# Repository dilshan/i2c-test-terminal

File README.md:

# I2C Master Mode Emulator

The I2C master mode emulator allows communication with I2C devices by sending or receiving data to/from the I2C bus. To issue the I2C commands, the emulator should connect to a PC over the USB port. After initializing the emulator, the PC and directly control the I2C slave chip/module.

This emulator is based on [ATmega16A](https://www.microchip.com/wwwproducts/en/ATmega16A) MCU. The USB communication channel is develop using the [V-USB](https://www.obdev.at/products/vusb/index.html) firmware.

To simplify the assembly, the PCB of this emulator is designed on a single-side board. The dimensions of the PCB are 96.77mm × 110.73mm. All the parts used in this project are through-hole-type, generally available components.

This emulator needs an external power supply, and the recommended supply voltage is between 12V - 15V.

The control software of the emulator is developed using libusb and tested only with *Linux* operating systems. The current firmware and control software support I2C emulation on 100kHz, 250kHz, and 400kHz clock rates.

Initially, we develop this emulator to work with 5V I2C devices, but later it has extended to work with 3.3V I2C devices. The 3.3V design is still under testing, and at the prototyping stage, we found a couple of issues in 3.3V mode.

In 3.3V mode, the required output level is available only if the emulator is in a "*ready*" state. In all the other states, it provides 5V output. **Therefore in 3.3V mode, necessary precautions need to be taken to protect the slave device from over-voltage damages.**

This project is an open-source hardware project. All the content of this project are distributed under the terms of the following license:

-   Hardware License: [CC BY 4.0](https://creativecommons.org/licenses/by/4.0/)
-   Software and firmware License: [MIT](https://github.com/dilshan/i2c-test-terminal/blob/main/LICENSE)
-   [Documentation](https://github.com/dilshan/i2c-test-terminal/wiki) License: [CC BY 4.0](https://creativecommons.org/licenses/by/4.0/)

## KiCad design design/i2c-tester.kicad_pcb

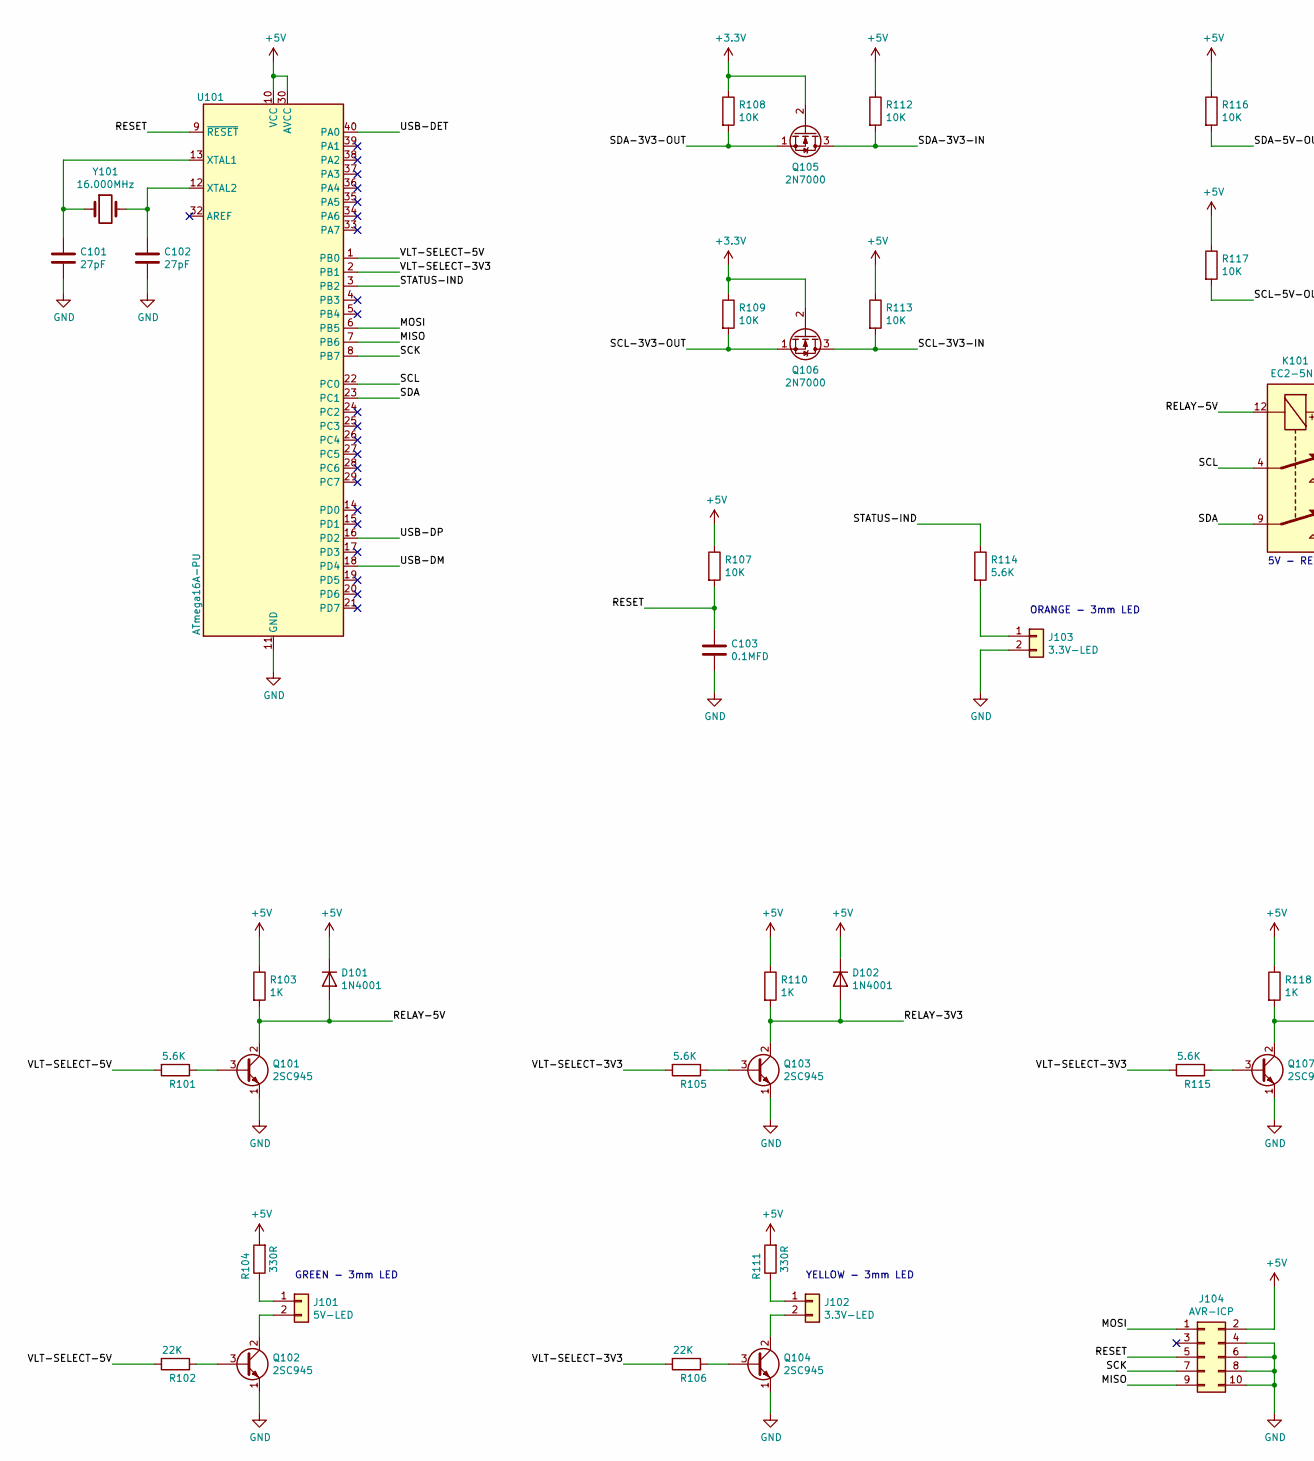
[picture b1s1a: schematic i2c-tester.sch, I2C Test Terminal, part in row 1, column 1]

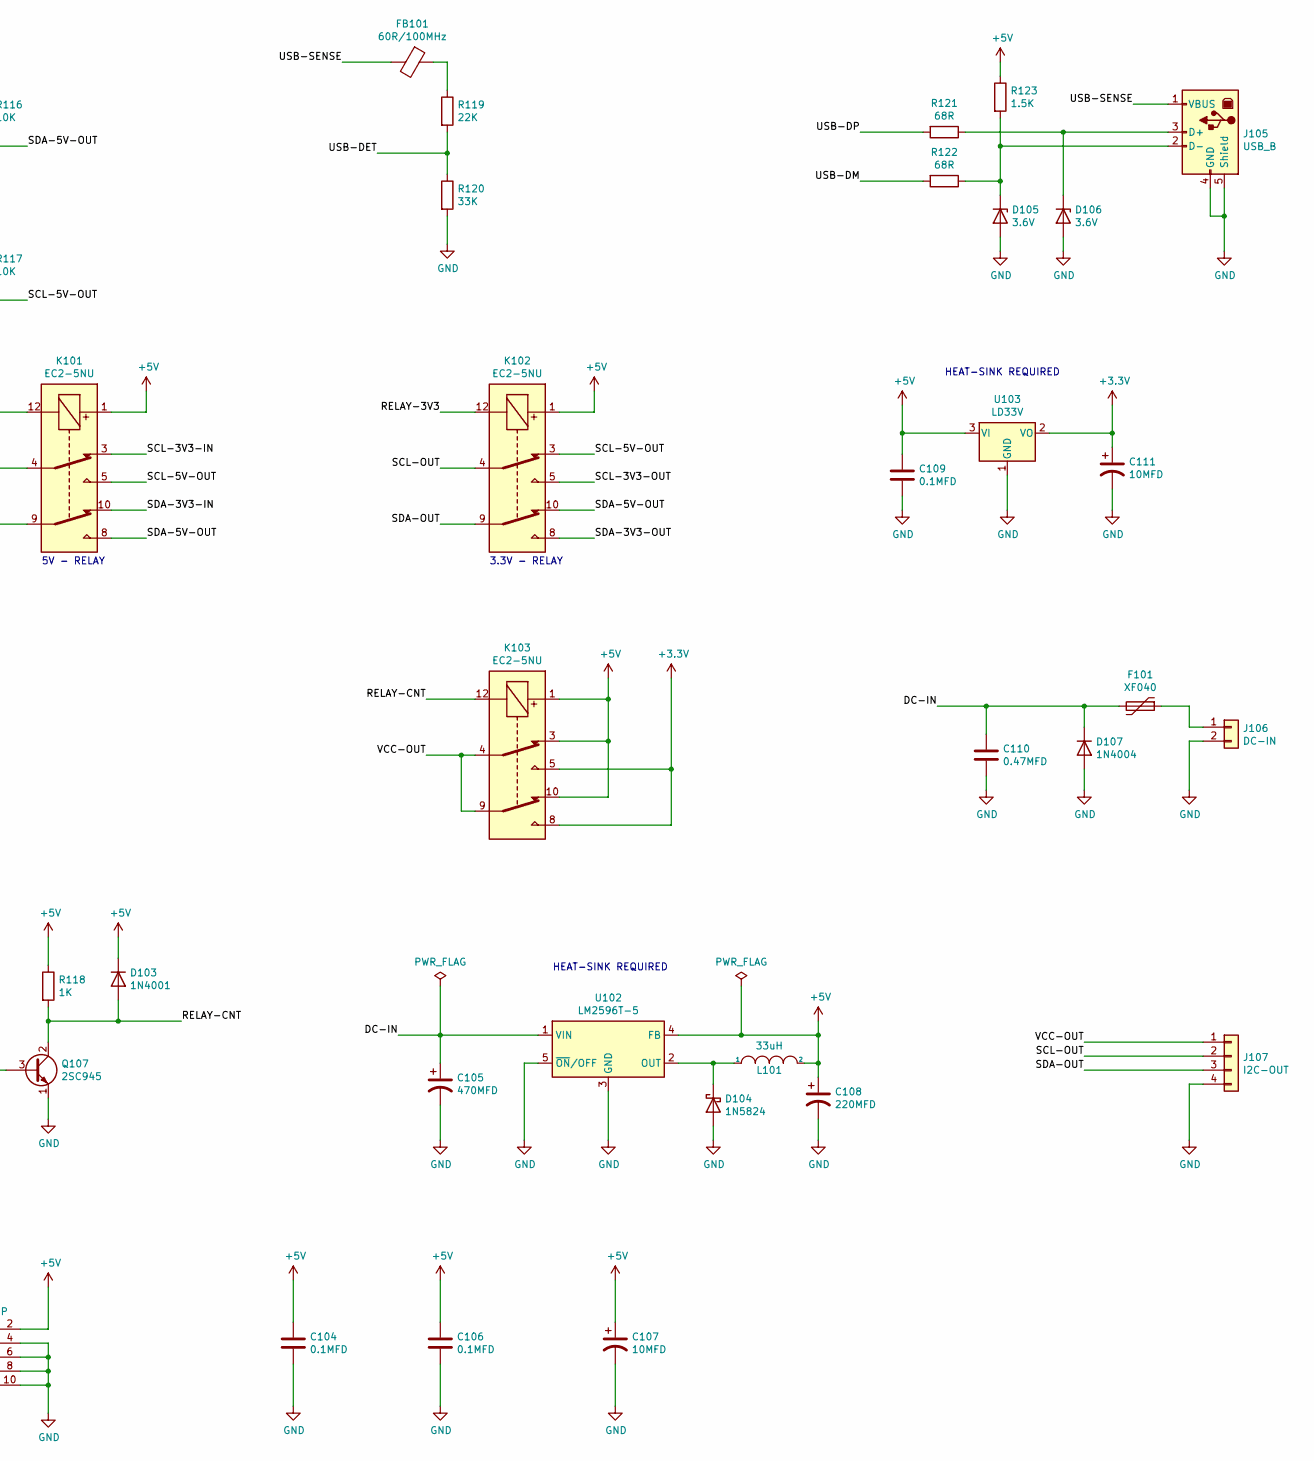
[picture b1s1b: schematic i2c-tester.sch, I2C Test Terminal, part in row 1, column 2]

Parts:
C101, C102: 27pF; C_Disc_D5.0mm_W2.5mm_P2.50mm
C103, C104, C106, C109: 0.1MFD; C_Disc_D12.5mm_W5.0mm_P10.00mm
C105: 470MFD; CP_Radial_D8.0mm_P3.50mm
C107, C111: 10MFD; CP_Radial_D5.0mm_P2.00mm
C108: 220MFD; CP_Radial_D6.3mm_P2.50mm
C110: 0.47MFD; C_Rect_L16.5mm_W7.0mm_P15.00mm_MKT
D101, D102, D103: 1N4001; D_DO-41_SOD81_P10.16mm_Horizontal
D104: 1N5824; D_DO-41_SOD81_P10.16mm_Horizontal
D105, D106: 3.6V; D_DO-35_SOD27_P7.62mm_Horizontal
D107: 1N4004; D_DO-41_SOD81_P10.16mm_Horizontal
F101: XF040; Fuse_Bourns_MF-RG300
FB101: 60R/100MHz; L_Axial_L6.6mm_D2.7mm_P10.16mm_Horizontal_Vishay_IM-2
J101: 5V-LED; PinHeader_1x02_P2.54mm_Vertical
J102, J103: 3.3V-LED; PinHeader_1x02_P2.54mm_Vertical
J104: AVR-ICP; PinHeader_2x05_P2.54mm_Vertical
J105: USB_B; USB_B_Lumberg_2411_02_Horizontal
J106: DC-IN; PhoenixContact_MCV_1,5_2-G-5.08_1x02_P5.08mm_Vertical
J107: I2C-OUT; PinHeader_1x04_P2.54mm_Vertical
K101, K102, K103: EC2-5NU; Relay_DPDT_Kemet_EC2
L101: 33uH; L_Toroid_Vertical_L14.0mm_W5.6mm_P5.30mm_Bourns_5700
Q101, Q102, Q103, Q104, Q107: 2SC945; TO-92_HandSolder
Q105, Q106: 2N7000; TO-92_HandSolder
R101, R105, R114, R115: 5.6K; R_Axial_DIN0309_L9.0mm_D3.2mm_P15.24mm_Horizontal
R102, R106, R119: 22K; R_Axial_DIN0309_L9.0mm_D3.2mm_P15.24mm_Horizontal
R103, R110, R118: 1K; R_Axial_DIN0309_L9.0mm_D3.2mm_P15.24mm_Horizontal
R104, R111: 330R; R_Axial_DIN0309_L9.0mm_D3.2mm_P15.24mm_Horizontal
R107, R108, R109, R112, R113, R116, R117: 10K; R_Axial_DIN0309_L9.0mm_D3.2mm_P15.24mm_Horizontal
R120: 33K; R_Axial_DIN0309_L9.0mm_D3.2mm_P15.24mm_Horizontal
R121, R122: 68R; R_Axial_DIN0309_L9.0mm_D3.2mm_P15.24mm_Horizontal
R123: 1.5K; R_Axial_DIN0309_L9.0mm_D3.2mm_P15.24mm_Horizontal
U101: ATmega16A-PU; DIP-40_W15.24mm_Socket_LongPads
U102: LM2596T-5; TO-220-5_P3.4x3.7mm_StaggerOdd_Lead3.8mm_Vertical
U103: LD33V; TO-220-3_Vertical
Y101: 16.000MHz; Crystal_HC49-U_Vertical

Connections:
+3V3: C111.1, K103.5, K103.8, Q105.2 (G), Q106.2 (G), R108.1, R109.1, U103.2 (VO)
+5V: C104.1, C106.1, C107.1, C108.1, C109.1, D101.1 (K), D102.1 (K), D103.1 (K), J104.2, K101.1, K102.1, K103.1, K103.3, K103.10, L101.2, R103.1, R104.2, R107.1, R110.1, R111.2, R112.1, R113.1, R116.1, R117.1, R118.1, R123.1, U101.10 (VCC), U101.30 (AVCC), U102.4 (FB), U103.3 (VI)
/DC-IN: C105.1, C110.1, D107.1 (K), F101.2, U102.1 (VIN)
/MISO: J104.9, U101.7 (PB6)
/MOSI: J104.1, U101.6 (PB5)
/RELAY-3V3: D102.2 (A), K102.12, Q103.2 (C), R110.2
/RELAY-5V: D101.2 (A), K101.12, Q101.2 (C), R103.2
/RELAY-CNT: D103.2 (A), K103.12, Q107.2 (C), R118.2
/RESET: C103.1, J104.5, R107.2, U101.9 (~RESET)
/SCK: J104.7, U101.8 (PB7)
/SCL: K101.4, U101.22 (PC0)
/SCL-3V3-IN: K101.3, Q106.3 (D), R113.2
/SCL-3V3-OUT: K102.5, Q106.1 (S), R109.2
/SCL-5V-OUT: K101.5, K102.3, R117.2
/SCL-OUT: J107.2, K102.4
/SDA: K101.9, U101.23 (PC1)
/SDA-3V3-IN: K101.10, Q105.3 (D), R112.2
/SDA-3V3-OUT: K102.8, Q105.1 (S), R108.2
/SDA-5V-OUT: K101.8, K102.10, R116.2
/SDA-OUT: J107.3, K102.9
/STATUS-IND: R114.1, U101.3 (PB2)
/USB-DET: R119.2, R120.1, U101.40 (PA0)
/USB-DM: R122.2, U101.18 (PD4)
/USB-DP: R121.2, U101.16 (PD2)
/USB-SENSE: FB101.2, J105.1 (VBUS)
/VCC-OUT: J107.1, K103.4, K103.9
/VLT-SELECT-3V3: R105.2, R106.2, R115.2, U101.2 (PB1)
/VLT-SELECT-5V: R101.2, R102.2, U101.1 (PB0)
GND: C101.2, C102.2, C103.2, C104.2, C105.2, C106.2, C107.2, C108.2, C109.2, C110.2, C111.2, D104.2 (A), D105.2 (A), D106.2 (A), D107.2 (A), J103.2, J104.4, J104.6, J104.8, J104.10, J105.4 (GND), J105.5 (Shield), J106.2, J107.4, Q101.1 (E), Q102.1 (E), Q103.1 (E), Q104.1 (E), Q107.1 (E), R120.2, U101.11 (GND), U101.31 (GND), U102.3 (GND), U102.5 (~ON~/OFF), U103.1 (GND)
unnamed: C101.1, U101.13 (XTAL1), Y101.1
unnamed: C102.1, U101.12 (XTAL2), Y101.2
unnamed: D104.1 (K), L101.1, U102.2 (OUT)
unnamed: D105.1 (K), J105.2 (D-), R122.1, R123.2
unnamed: D106.1 (K), J105.3 (D+), R121.1
unnamed: F101.1, J106.1
unnamed: FB101.1, R119.1
unnamed: J101.1, R104.1
unnamed: J101.2, Q102.2 (C)
unnamed: J102.1, R111.1
unnamed: J102.2, Q104.2 (C)
unnamed: J103.1, R114.2
unnamed: Q101.3 (B), R101.1
unnamed: Q102.3 (B), R102.1
unnamed: Q103.3 (B), R105.1
unnamed: Q104.3 (B), R106.1
unnamed: Q107.3 (B), R115.1

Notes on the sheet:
5V - RELAY
3.3V - RELAY
GREEN - 3mm LED
YELLOW - 3mm LED
ORANGE - 3mm LED
HEAT-SINK REQUIRED

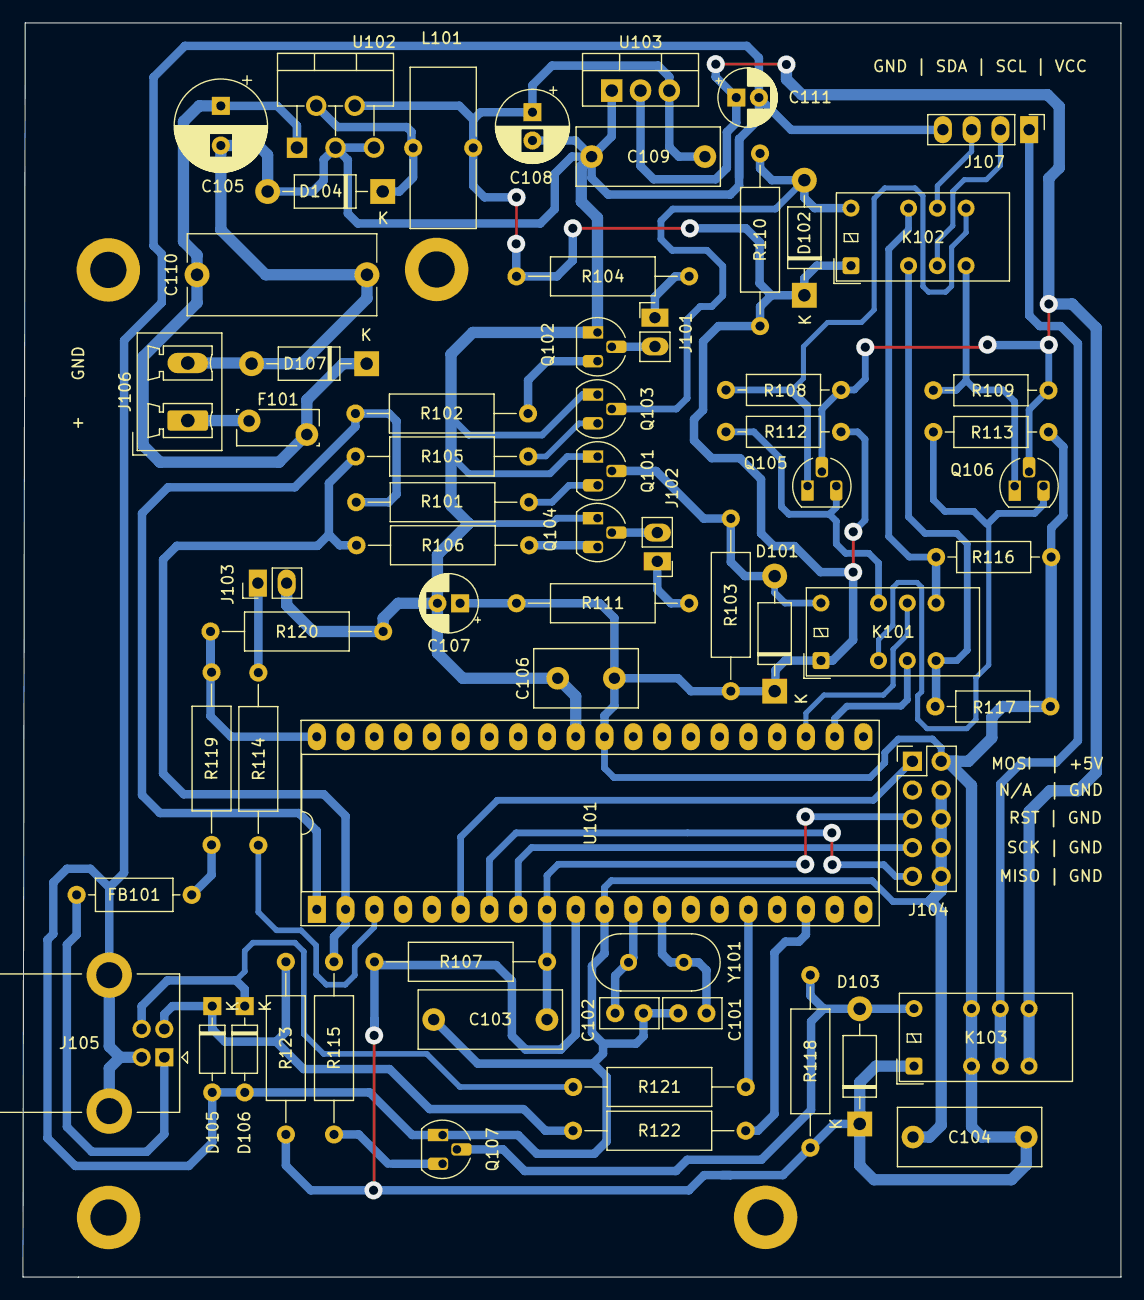
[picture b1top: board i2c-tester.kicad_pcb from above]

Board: 2 copper layers, 96.9 x 110.7 mm, 65 parts (0 on the bottom side), 46 nets.

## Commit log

2021-03-15 Initial version of I2C Test Terminal source files and design files.
2021-03-15 Add enclosure label, design file and output file.
2021-03-16 Initial readme file update.
2021-03-16 Add image of the finished prototype and link it to readme.md file.
2021-03-16 Fix URL issue in software license.
2021-03-16 Add PDF version of the current schematic.
2021-03-16 Fix minor lanugage issues in help / documentation.
2021-03-16 Add Fritzing diagram to show the test connection layout.
2021-03-16 Update readme.md file with documentation link.
